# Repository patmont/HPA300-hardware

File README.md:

# HPA300 replacement controller hardware

An open-hardware, ESP32-S2 replacement control board for the Honeywell HPA300
air purifier. The board preserves the original front-panel layout while adding
USB-C, native USB programming, and a controller designed for the companion
[HPA300 firmware](https://github.com/patmont/HPA300-firmware).

> [!IMPORTANT]
> This is an independent community project. It is not affiliated with,
> authorized by, or endorsed by Honeywell International Inc. Build and install
> it at your own risk.

## Downloads

| I want to... | Get this |
| --- | --- |
| Read the circuit | [Schematic PDF](HPA300.pdf) |
| Order the parts | [DigiKey shared list](https://www.digikey.com/en/mylists/list/1ANK154NOU) or [versioned BOM](manufacturing/Assembly/HPA300-bom.csv) |
| Order a bare PCB | Download the `HPA300-<version>-gerbers.zip` asset from the [latest release](https://github.com/patmont/HPA300-hardware/releases/latest) |
| Modify the design | Open [HPA300.kicad_pro](HPA300.kicad_pro) in KiCad 9 |
| Build or flash firmware | Visit [HPA300-firmware](https://github.com/patmont/HPA300-firmware) |

Release assets are the recommended manufacturing handoff because they are tied
to a tagged revision and include SHA-256 checksums. The files under
`manufacturing/` are reviewable snapshots; do not mix them with source files
from a different commit.

## Hardware overview

- ESP32-S2-SOLO-2 controller with native USB-C
- Six capacitive-touch keys matching the original control panel
- Nine front-panel indicators with PWM brightness control
- 74HC238 fan-speed selection with a hardware-disabled default state
- Boot, reset, Tag-Connect programming, and power test access
- Two-layer, 1.6 mm PCB designed in KiCad 9
- Approximately 245 mm × 51 mm overall outline, including the shaped edges

The current checked-in design is revision A and corresponds to the as-built
board. Before ordering, inspect the schematic, board outline, connector
orientation, and your purifier revision. This project has not been evaluated or
certified by a safety agency.

## Manufacturing

For a bare PCB, upload only the release's Gerber archive to the fabricator. It
contains copper, solder mask, paste, silkscreen, edge cuts, plated drills, and
non-plated drills. The archive is generated from the tracked files in
[`manufacturing/Fabrication`](manufacturing/Fabrication/).

The [DigiKey list](https://www.digikey.com/en/mylists/list/1ANK154NOU) is the
most convenient shopping list. The repository BOM is version controlled so a
release remains reproducible even if the shared list later changes. Check stock,
manufacturer part numbers, substitutions, and do-not-populate items before
ordering.

The current repository does **not** claim to be a turnkey PCBA package. An
assembly house will also need a placement/centroid file, confirmed rotations,
assembly drawings, and instructions for the through-hole and mechanical parts.
See [manufacturing/README.md](manufacturing/README.md) for the artifact manifest
and release procedure.

To build the same release assets locally from PowerShell:

```powershell
./scripts/package-release.ps1 -Version v0.1.0
```

The packages are written to `dist/`, which is intentionally ignored by Git.
Pushing a `v*` tag runs the same packager in GitHub Actions and creates a GitHub
release with the Gerber ZIP, schematic PDF, BOM, license notice, and checksum
manifest.

## Repository layout

```text
HPA300.kicad_pro         KiCad project entry point
HPA300.kicad_pcb         Editable PCB source
HPA300.kicad_sch         Root schematic and hierarchical sheets
*.kicad_sch
lib/                     Project-specific symbols, footprints, and 3D models
graphics/                Board renders, logo, and open-hardware mark
manufacturing/
  Fabrication/           Gerber and drill snapshot
  Assembly/              Version-controlled BOM
scripts/                 Reproducible release packaging
.github/workflows/       CI and tagged-release automation
```

KiCad backups, local preferences, caches, downloaded datasheets, and generated
release archives are excluded from version control. Custom symbols, footprints,
and 3D models required to open the project are kept in `lib/`.

## Contributing

Open an issue before making a change that affects the board outline, original
appliance interface, fan safety behavior, or manufacturing stack-up. For a
design change, update the editable KiCad source first, run KiCad's electrical
and design-rule checks, then regenerate the PDF, BOM, Gerbers, and drill files
together. Include the KiCad version and rule-check results in the pull request.

## License and attribution

The hardware design and associated source are licensed under the
[CERN Open Hardware Licence Version 2 – Weakly Reciprocal](LICENSE). You may
study, modify, make, and sell products based on the design, but the license
requires preservation of notices and corresponding-source obligations. See
[NOTICE.md](NOTICE.md) for the copyright, source-location, attribution, and
trademark notices that travel with the design.

Commercial use cannot be prohibited while also calling the project open-source
hardware. The reciprocal license and source-location notice are intended to
ensure that commercial derivatives remain attributable and that their design
changes are available to recipients.

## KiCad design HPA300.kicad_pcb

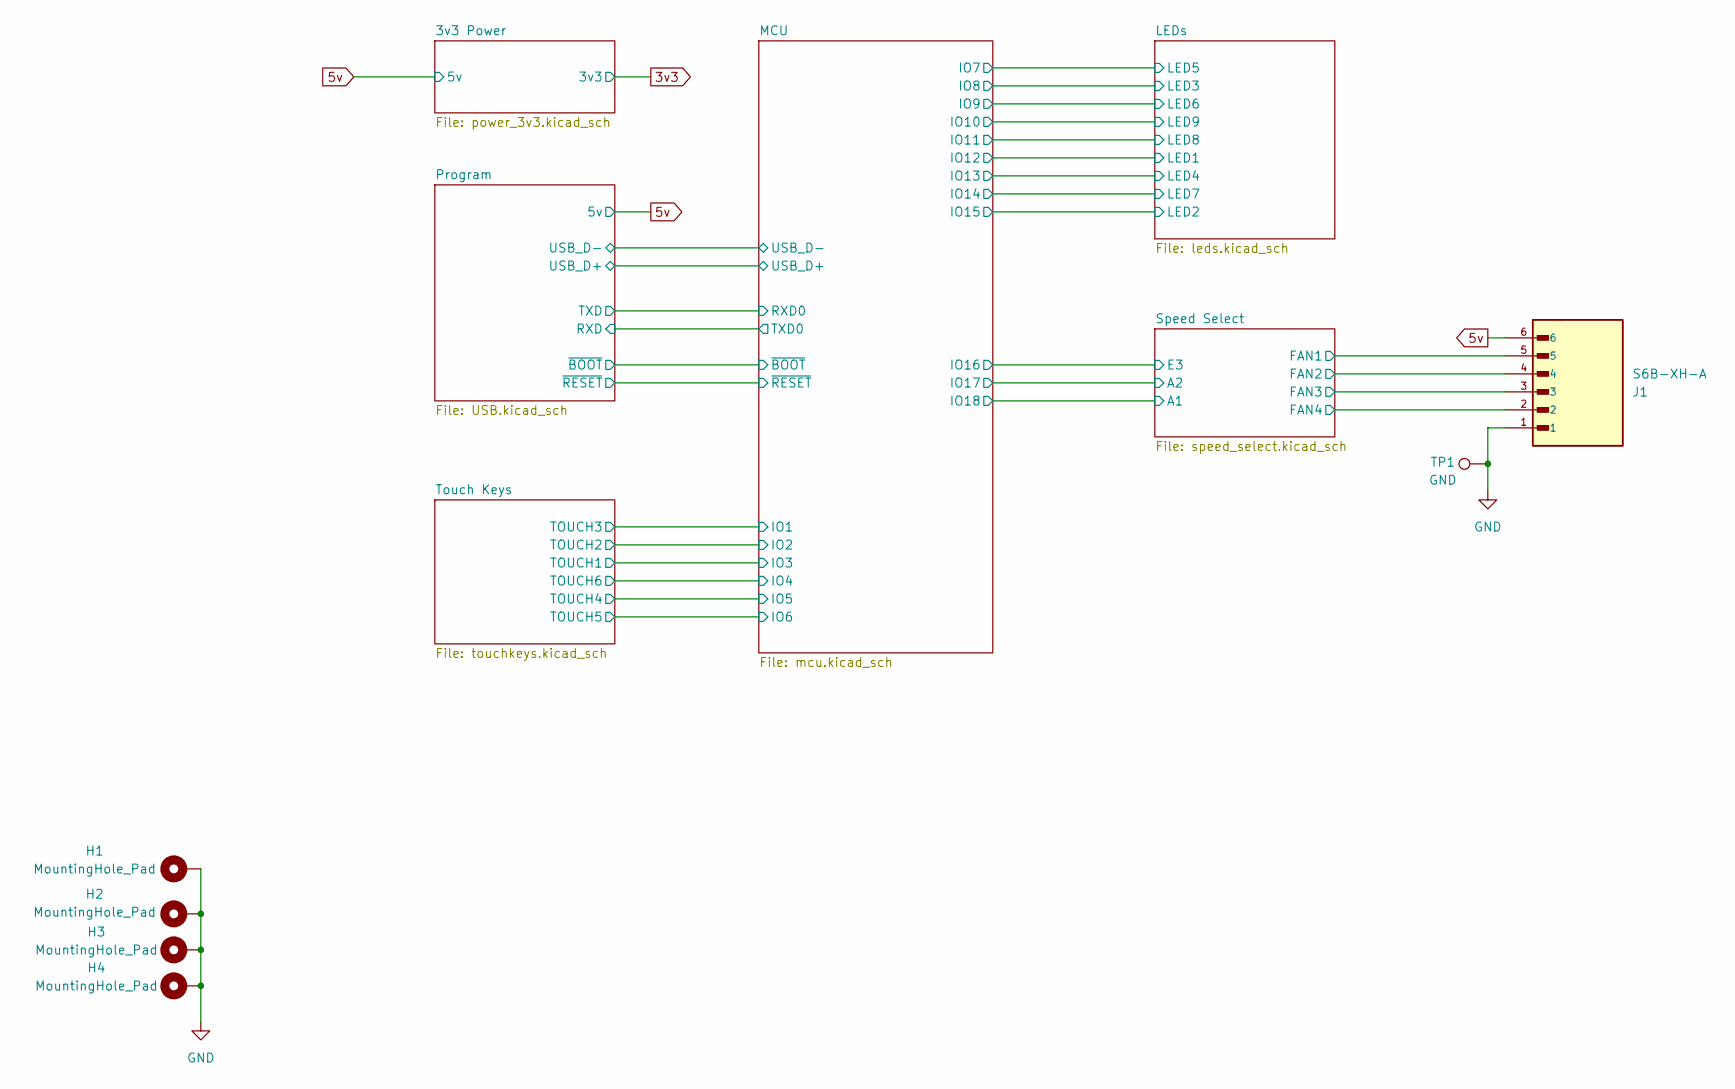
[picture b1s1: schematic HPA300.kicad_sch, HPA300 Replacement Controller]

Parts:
H1, H2, H3, H4: MountingHole_Pad; MountingHole_3.5mm_Pad_Via
J1: S6B-XH-A; JST_S6B-XH-A; Digikey S6B-XH-A
TP1: GND; TestPoint_Pad_D1.0mm

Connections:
5v: J1.6; also elsewhere on the board
/Speed Select/FAN1: J1.5; also elsewhere on the board
/Speed Select/FAN2: J1.4; also elsewhere on the board
/Speed Select/FAN3: J1.3; also elsewhere on the board
/Speed Select/FAN4: J1.2; also elsewhere on the board
GND: H1.1, H2.1, H3.1, H4.1, J1.1, TP1.1; also elsewhere on the board

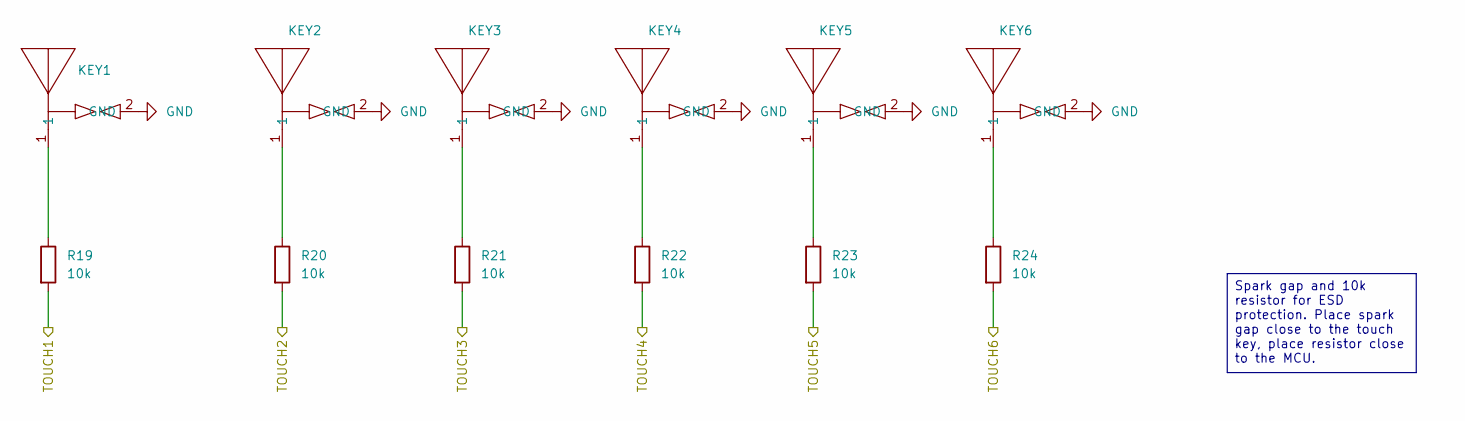
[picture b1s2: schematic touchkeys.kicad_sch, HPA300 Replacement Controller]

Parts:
KEY1, KEY2, KEY3, KEY4, KEY5, KEY6: HPA300 Key
R19, R20, R21, R22, R23, R24: 10k; R_0805_2012Metric; Digikey CRCW080510K0FKEA

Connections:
/MCU/IO1: R21.2; also elsewhere on the board
/MCU/IO2: R20.2; also elsewhere on the board
/MCU/IO3: R19.2; also elsewhere on the board
/MCU/IO4: R24.2; also elsewhere on the board
/MCU/IO5: R22.2; also elsewhere on the board
/MCU/IO6: R23.2; also elsewhere on the board
GND: KEY1.2 (GND), KEY2.2 (GND), KEY3.2 (GND), KEY4.2 (GND), KEY5.2 (GND), KEY6.2 (GND); also elsewhere on the board
unnamed: KEY1.1, R19.1
unnamed: KEY2.1, R20.1
unnamed: KEY3.1, R21.1
unnamed: KEY4.1, R22.1
unnamed: KEY5.1, R23.1
unnamed: KEY6.1, R24.1

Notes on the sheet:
Spark gap and 10k resistor for ESD protection. Place spark gap close to the touch key, place resistor close to the MCU.

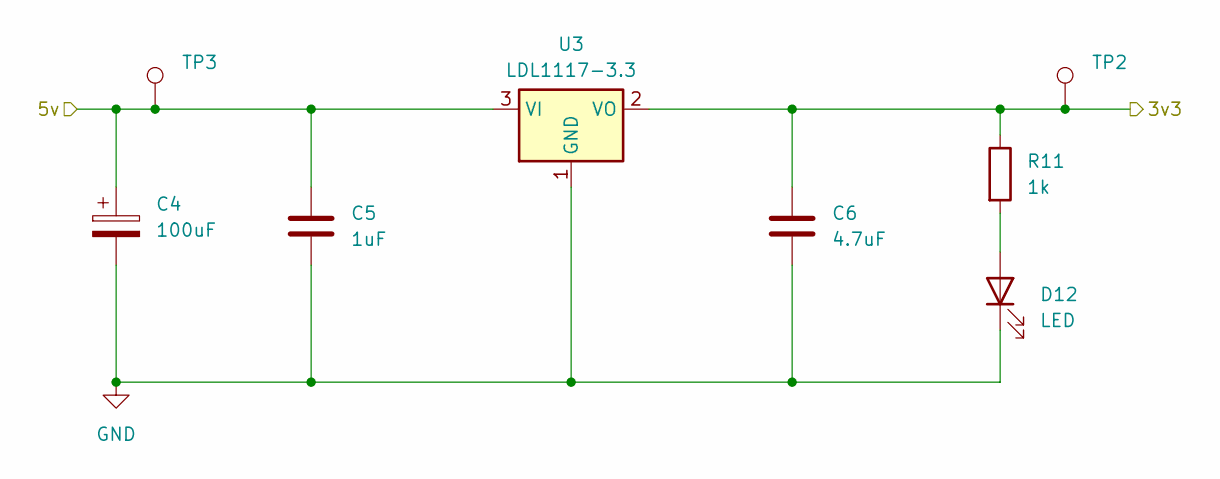
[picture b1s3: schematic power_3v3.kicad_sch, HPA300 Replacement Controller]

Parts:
C4: 100uF; CP_Elec_6.3x5.8; Digikey UUD1C101MCL1GS
C5: 1uF; C_0805_2012Metric; Digikey GRM21BR61C105MA01L
C6: 4.7uF; C_1206_3216Metric; Digikey GRM319R61H475KA12D
D12: LED; LED_0805_2012Metric; Digikey LTST-C170GKT
R11: 1k; R_0805_2012Metric; Digikey CRCW08051K00FKEA
TP2: 3.3V; TestPoint_Pad_D1.0mm
TP3: 5V; TestPoint_Pad_D1.0mm
U3: LDL1117-3.3; SOT-223-3_TabPin2; Digikey LDL1117S33R

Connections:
3v3: C6.1, R11.1, TP2.1, U3.2 (VO); also elsewhere on the board
5v: C4.1, C5.1, TP3.1, U3.3 (VI); also elsewhere on the board
GND: C4.2, C5.2, C6.2, D12.1 (K), U3.1 (GND); also elsewhere on the board
unnamed: D12.2 (A), R11.2

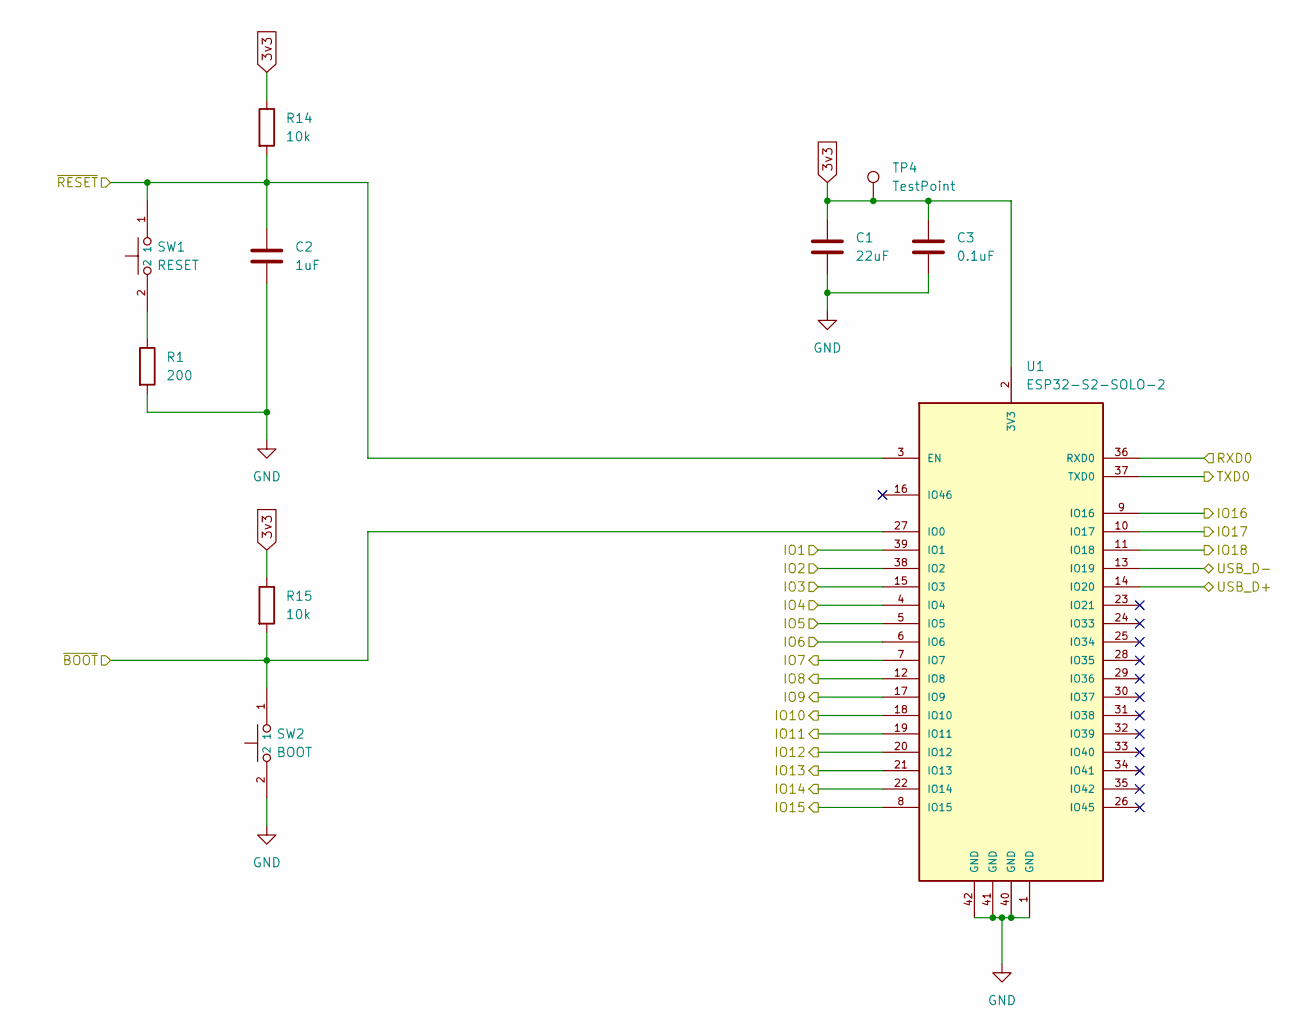
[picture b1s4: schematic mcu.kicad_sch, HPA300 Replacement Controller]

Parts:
C1: 22uF; C_1206_3216Metric; Digikey CL31A226KAHNNNE
C2: 1uF; C_0805_2012Metric; Digikey GRM21BR61C105MA01L
C3: 0.1uF; C_0805_2012Metric; Digikey KGM21KR51H104KU
R1: 200; R_0805_2012Metric; Digikey CRCW0805200RFKEAC
R14, R15: 10k; R_0805_2012Metric; Digikey CRCW080510K0FKEA
SW1: RESET; SW_B3U-1100P; Digikey B3U-1100P
SW2: BOOT; SW_B3U-1100P; Digikey B3U-1100P
TP4: TestPoint; TestPoint_Pad_D1.0mm
U1: ESP32-S2-SOLO-2; PARTREV 1.6; Digikey ESP32-S2-SOLO-2-N4

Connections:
3v3: C1.1, C3.1, R14.1, R15.1, TP4.1, U1.2 (3V3); also elsewhere on the board
/LEDs/LED1: U1.20 (IO12); also elsewhere on the board
/LEDs/LED2: U1.8 (IO15); also elsewhere on the board
/LEDs/LED3: U1.12 (IO8); also elsewhere on the board
/LEDs/LED4: U1.21 (IO13); also elsewhere on the board
/LEDs/LED5: U1.7 (IO7); also elsewhere on the board
/LEDs/LED6: U1.17 (IO9); also elsewhere on the board
/LEDs/LED7: U1.22 (IO14); also elsewhere on the board
/LEDs/LED8: U1.19 (IO11); also elsewhere on the board
/LEDs/LED9: U1.18 (IO10); also elsewhere on the board
/MCU/IO1: U1.39 (IO1); also elsewhere on the board
/MCU/IO2: U1.38 (IO2); also elsewhere on the board
/MCU/IO3: U1.15 (IO3); also elsewhere on the board
/MCU/IO4: U1.4 (IO4); also elsewhere on the board
/MCU/IO5: U1.5 (IO5); also elsewhere on the board
/MCU/IO6: U1.6 (IO6); also elsewhere on the board
/MCU/IO16: U1.9 (IO16); also elsewhere on the board
/MCU/IO17: U1.10 (IO17); also elsewhere on the board
/MCU/IO18: U1.11 (IO18); also elsewhere on the board
/MCU/RXD0: U1.36 (RXD0); also elsewhere on the board
/MCU/TXD0: U1.37 (TXD0); also elsewhere on the board
/MCU/USB_D+: U1.14 (IO20); also elsewhere on the board
/MCU/USB_D-: U1.13 (IO19); also elsewhere on the board
/MCU/~BOOT: R15.2, SW2.1, U1.27 (IO0); also elsewhere on the board
/MCU/~RESET: C2.1, R14.2, SW1.1, U1.3 (EN); also elsewhere on the board
GND: C1.2, C2.2, C3.2, R1.2, SW2.2, U1.1 (GND), U1.40 (GND), U1.41 (GND), U1.42 (GND); also elsewhere on the board
unnamed: R1.1, SW1.2

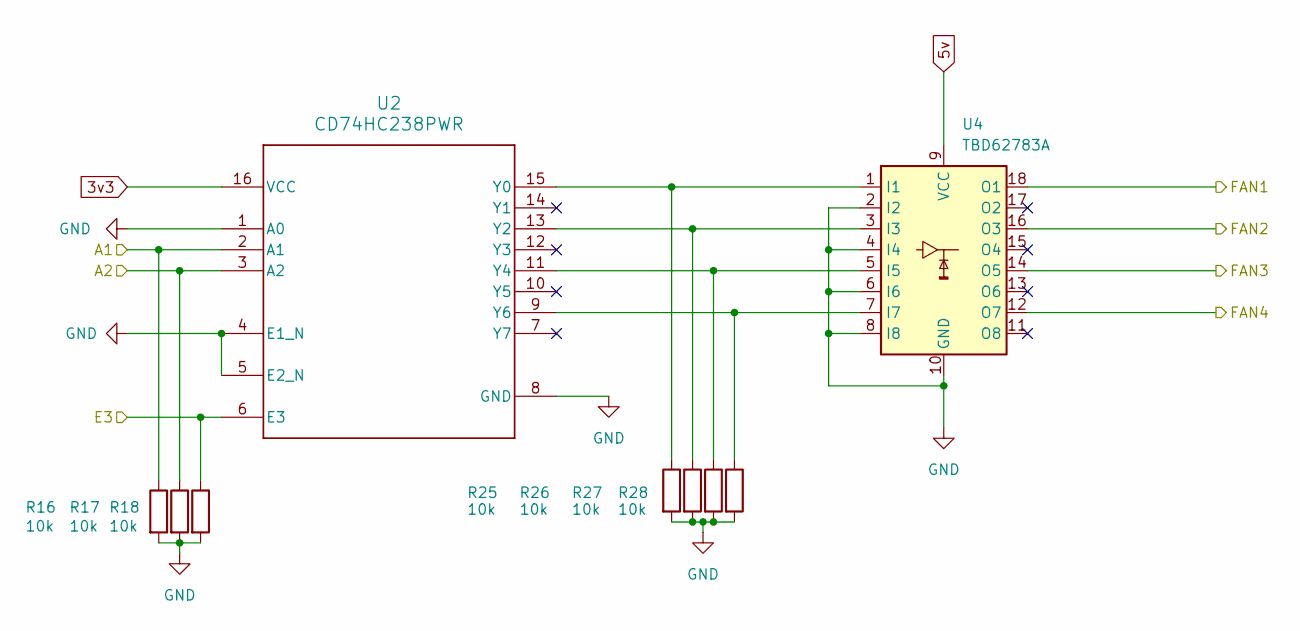
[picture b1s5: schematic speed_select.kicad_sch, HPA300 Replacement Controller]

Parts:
R16, R17, R18, R25, R26, R27, R28: 10k; R_0805_2012Metric; Digikey CRCW080510K0FKEA
U2: CD74HC238PWR; PW0016A_N; Digikey CD74HC238PWR
U4: TBD62783A; SSOP-18_4.4x6.5mm_P0.65mm; Digikey TBD62783AFNG,EL

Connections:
3v3: U2.16 (VCC); also elsewhere on the board
5v: U4.9 (VCC); also elsewhere on the board
/MCU/IO16: R18.1, U2.6 (E3); also elsewhere on the board
/MCU/IO17: R17.1, U2.3 (A2); also elsewhere on the board
/MCU/IO18: R16.1, U2.2 (A1); also elsewhere on the board
/Speed Select/FAN1: U4.18 (O1); also elsewhere on the board
/Speed Select/FAN2: U4.16 (O3); also elsewhere on the board
/Speed Select/FAN3: U4.14 (O5); also elsewhere on the board
/Speed Select/FAN4: U4.12 (O7); also elsewhere on the board
GND: R16.2, R17.2, R18.2, R25.2, R26.2, R27.2, R28.2, U2.1 (A0), U2.4 (E1_N), U2.5 (E2_N), U2.8 (GND), U4.2 (I2), U4.4 (I4), U4.6 (I6), U4.8 (I8), U4.10 (GND); also elsewhere on the board
unnamed: R25.1, U2.15 (Y0), U4.1 (I1)
unnamed: R26.1, U2.13 (Y2), U4.3 (I3)
unnamed: R27.1, U2.11 (Y4), U4.5 (I5)
unnamed: R28.1, U2.9 (Y6), U4.7 (I7)

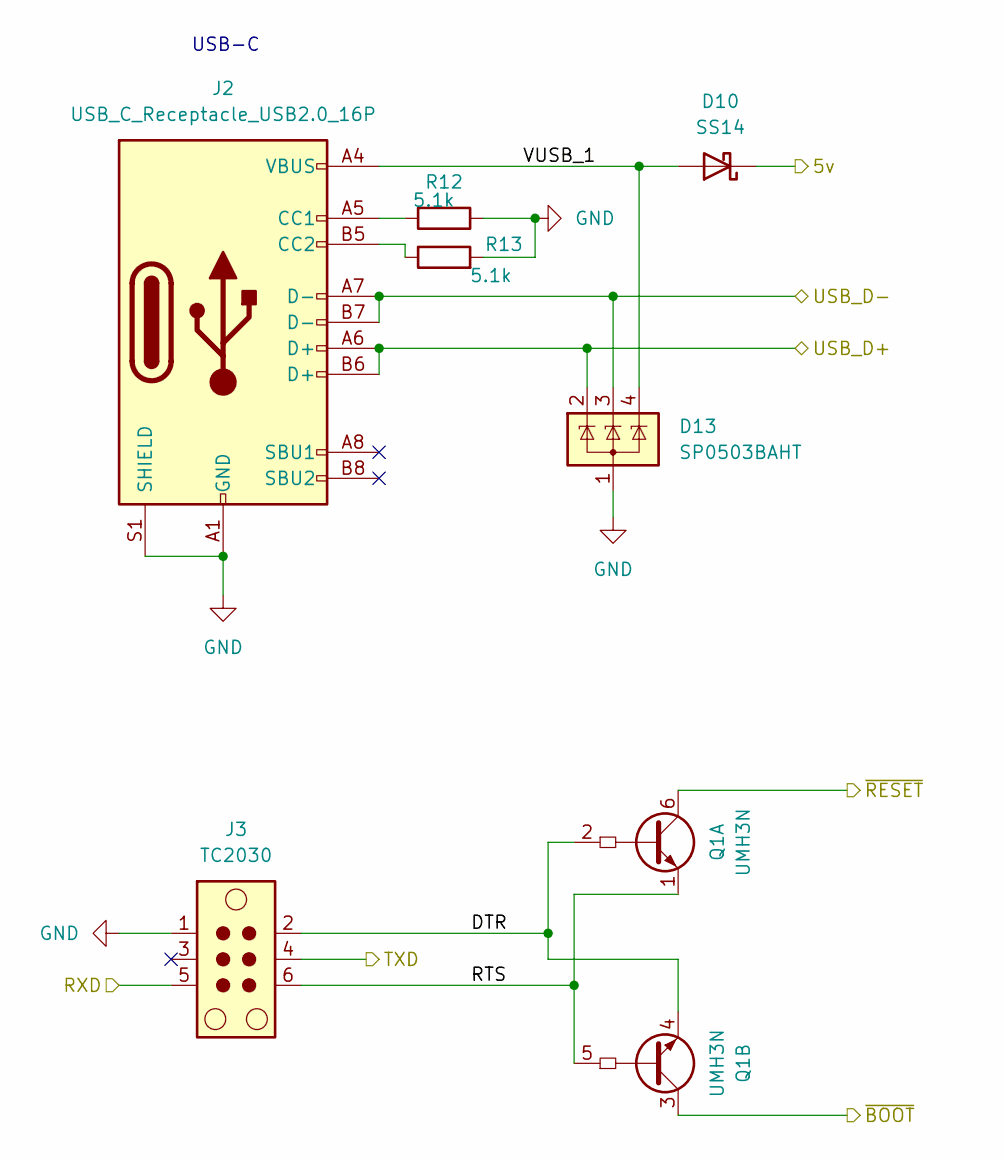
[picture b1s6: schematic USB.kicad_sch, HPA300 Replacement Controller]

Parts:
D10: SS14; D_SMA; Digikey B140Q-13-F
D13: SP0503BAHT; SOT-143; Digikey SP0503BAHTG
J2: USB_C_Receptacle_USB2.0_16P; USB_C_Receptacle_GCT_USB4110; Digikey USB4110-GF-A
J3: TC2030; Tag-Connect_TC2030-IDC-NL_2x03_P1.27mm_Vertical
Q1: UMH3N; SOT-363_SC-70-6; Digikey UMH3NFHATN
R12, R13: 5.1k; R_0805_2012Metric; Digikey CRCW08055K10FKEA

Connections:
5v: D10.1 (K); also elsewhere on the board
/MCU/RXD0: J3.4; also elsewhere on the board
/MCU/TXD0: J3.5; also elsewhere on the board
/MCU/USB_D+: D13.2 (K), J2.A6 (D+), J2.B6 (D+); also elsewhere on the board
/MCU/USB_D-: D13.3 (K), J2.A7 (D-), J2.B7 (D-); also elsewhere on the board
/MCU/~BOOT: Q1.3 (C2); also elsewhere on the board
/MCU/~RESET: Q1.6 (C1); also elsewhere on the board
/Program/DTR: J3.2, Q1.2 (B1), Q1.4 (E2)
/Program/RTS: J3.6, Q1.1 (E1), Q1.5 (B2)
/Program/VUSB_1: D10.2 (A), D13.4 (K), J2.A4 (VBUS), J2.A9 (VBUS), J2.B4 (VBUS), J2.B9 (VBUS)
GND: D13.1 (A), J2.A1 (GND), J2.A12 (GND), J2.B1 (GND), J2.B12 (GND), J2.S1 (SHIELD), J3.1, R12.1, R13.2; also elsewhere on the board
unnamed: J2.A5 (CC1), R12.2
unnamed: J2.B5 (CC2), R13.1

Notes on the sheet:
USB-C

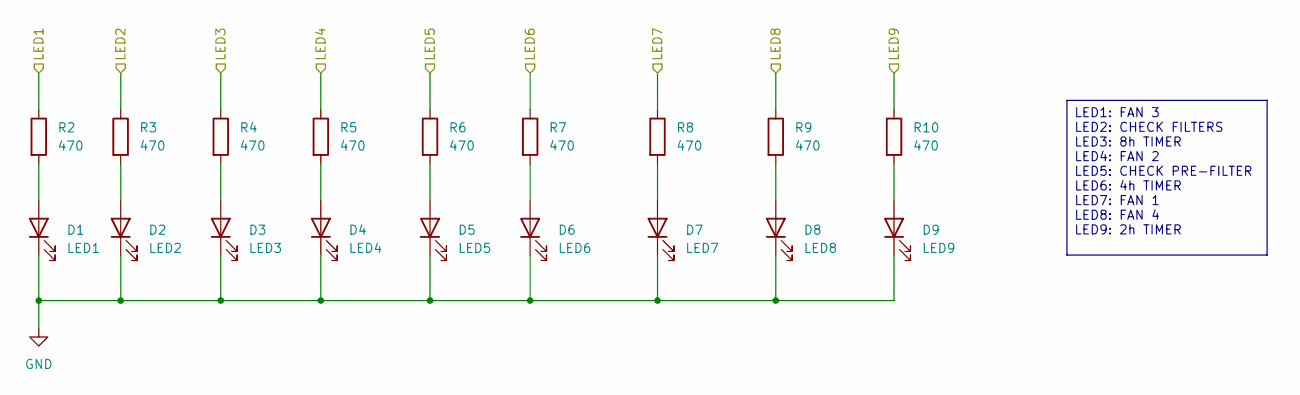
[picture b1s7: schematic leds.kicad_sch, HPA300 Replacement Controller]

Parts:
D1: LED1; LED_D3.0mm; Digikey 151031SS04000
D2: LED2; LED_D3.0mm; Digikey 151031SS04000
D3: LED3; LED_D3.0mm; Digikey 151031SS04000
D4: LED4; LED_D3.0mm; Digikey 151031SS04000
D5: LED5; LED_D3.0mm; Digikey 151031SS04000
D6: LED6; LED_D3.0mm; Digikey 151031SS04000
D7: LED7; LED_D3.0mm; Digikey 151031SS04000
D8: LED8; LED_D3.0mm; Digikey 151031SS04000
D9: LED9; LED_D3.0mm; Digikey 151031SS04000
R2, R3, R4, R5, R6, R7, R8, R9, R10: 470; R_0805_2012Metric; Digikey CRGCQ0805J470R

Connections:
/LEDs/LED1: R2.1; also elsewhere on the board
/LEDs/LED2: R3.1; also elsewhere on the board
/LEDs/LED3: R4.1; also elsewhere on the board
/LEDs/LED4: R5.1; also elsewhere on the board
/LEDs/LED5: R6.1; also elsewhere on the board
/LEDs/LED6: R7.1; also elsewhere on the board
/LEDs/LED7: R8.1; also elsewhere on the board
/LEDs/LED8: R9.1; also elsewhere on the board
/LEDs/LED9: R10.1; also elsewhere on the board
GND: D1.1 (K), D2.1 (K), D3.1 (K), D4.1 (K), D5.1 (K), D6.1 (K), D7.1 (K), D8.1 (K), D9.1 (K); also elsewhere on the board
unnamed: D1.2 (A), R2.2
unnamed: D2.2 (A), R3.2
unnamed: D3.2 (A), R4.2
unnamed: D4.2 (A), R5.2
unnamed: D5.2 (A), R6.2
unnamed: D6.2 (A), R7.2
unnamed: D7.2 (A), R8.2
unnamed: D8.2 (A), R9.2
unnamed: D9.2 (A), R10.2

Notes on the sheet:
LED1: FAN 3 LED2: CHECK FILTERS LED3: 8h TIMER LED4: FAN 2 LED5: CHECK PRE-FILTER LED6: 4h TIMER LED7: FAN 1 LED8: FAN 4 LED9: 2h TIMER

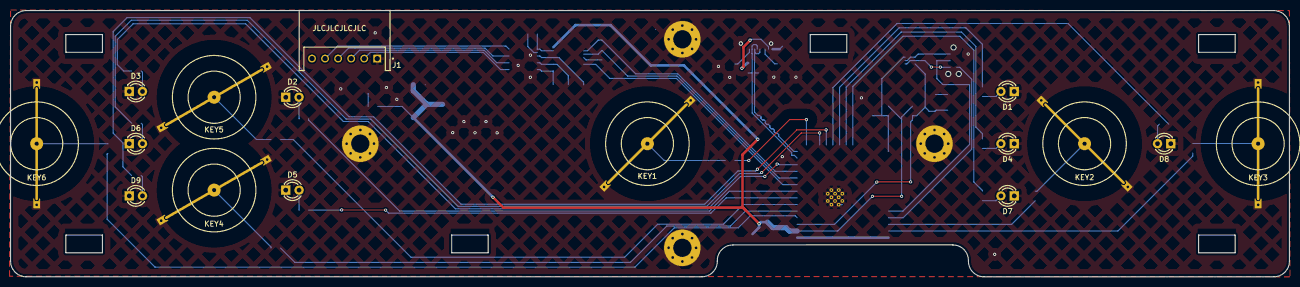
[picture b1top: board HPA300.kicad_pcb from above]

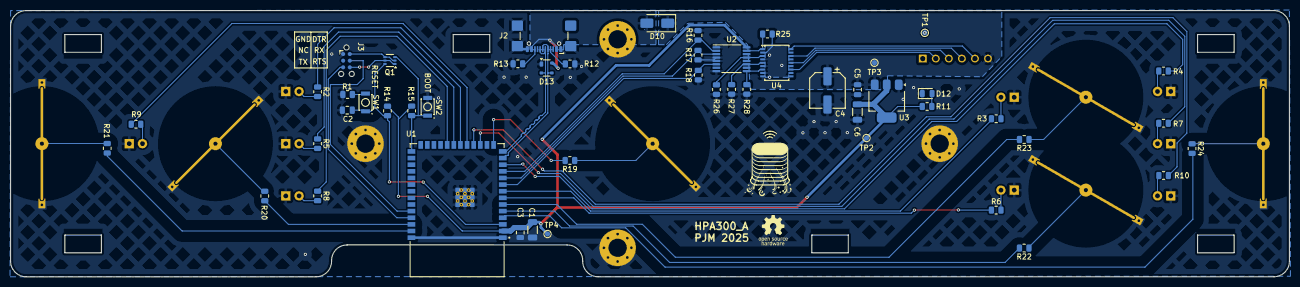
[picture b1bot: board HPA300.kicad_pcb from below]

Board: 2 copper layers, 245.0 x 51.0 mm, 70 parts (50 on the bottom side), 57 nets.

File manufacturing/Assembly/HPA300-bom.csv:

"Reference","Qty","Value","DNP","Exclude from BOM","Exclude from Board","Footprint","Datasheet","Digikey"
"C1","1","22uF","","","","Capacitor_SMD:C_1206_3216Metric","~","CL31A226KAHNNNE"
"C2,C5","2","1uF","","","","Capacitor_SMD:C_0805_2012Metric","~","GRM21BR61C105MA01L"
"C3","1","0.1uF","","","","Capacitor_SMD:C_0805_2012Metric","~","KGM21KR51H104KU"
"C4","1","100uF","","","","Capacitor_SMD:CP_Elec_6.3x5.8","https://www.nichicon.co.jp/english/series_items/catalog_pdf/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","UUD1C101MCL1GS"
"C6","1","4.7uF","","","","Capacitor_SMD:C_1206_3216Metric","~","GRM319R61H475KA12D"
"D1","1","LED1","","","","LED_THT:LED_D3.0mm","~","151031SS04000"
"D2","1","LED2","","","","LED_THT:LED_D3.0mm","~","151031SS04000"
"D3","1","LED3","","","","LED_THT:LED_D3.0mm","~","151031SS04000"
"D4","1","LED4","","","","LED_THT:LED_D3.0mm","~","151031SS04000"
"D5","1","LED5","","","","LED_THT:LED_D3.0mm","~","151031SS04000"
"D6","1","LED6","","","","LED_THT:LED_D3.0mm","~","151031SS04000"
"D7","1","LED7","","","","LED_THT:LED_D3.0mm","~","151031SS04000"
"D8","1","LED8","","","","LED_THT:LED_D3.0mm","~","151031SS04000"
"D9","1","LED9","","","","LED_THT:LED_D3.0mm","~","151031SS04000"
"D10","1","SS14","","","","Diode_SMD:D_SMA","https://www.vishay.com/docs/88746/ss12.pdf","B140Q-13-F"
"D12","1","LED","","","","LED_SMD:LED_0805_2012Metric","~","LTST-C170GKT"
"D13","1","SP0503BAHT","","","","Package_TO_SOT_SMD:SOT-143","http://www.littelfuse.com/~/media/files/littelfuse/technical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"," SP0503BAHTG"
"H1,H2,H3,H4","4","MountingHole_Pad","","Excluded from BOM","","MountingHole:MountingHole_3.5mm_Pad_Via","~",""
"J1","1","S6B-XH-A","","","","0_connector:JST_S6B-XH-A","","S6B-XH-A"
"J2","1","USB_C_Receptacle_USB2.0_16P","","","","Connector_USB:USB_C_Receptacle_GCT_USB4110","https://www.usb.org/sites/default/files/documents/usb_type-c.zip"," USB4110-GF-A"
"J3","1","TC2030","","Excluded from BOM","","Connector:Tag-Connect_TC2030-IDC-NL_2x03_P1.27mm_Vertical","https://www.tag-connect.com/wp-content/uploads/bsk-pdf-manag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",""
"KEY1,KEY2,KEY3,KEY4,KEY5,KEY6","6","~","","","","0_switch:HPA300 Key","",""
"Q1","1","UMH3N","","","","Package_TO_SOT_SMD:SOT-363_SC-70-6","http://rohmfs.rohm.com/en/products/databook/datasheet/discre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","UMH3NFHATN"
"R1","1","200","","","","Resistor_SMD:R_0805_2012Metric","~","CRCW0805200RFKEAC"
"R2,R3,R4,R5,R6,R7,R8,R9,R10","9","470","","","","Resistor_SMD:R_0805_2012Metric","~","CRGCQ0805J470R"
"R11","1","1k","","","","Resistor_SMD:R_0805_2012Metric","~","CRCW08051K00FKEA"
"R12,R13","2","5.1k","","","","Resistor_SMD:R_0805_2012Metric","~","CRCW08055K10FKEA"
"R14,R15,R16,R17,R18,R19,R20,R21,R22,R23,R24,R25,R26,R27,R28","15","10k","","","","Resistor_SMD:R_0805_2012Metric","~","CRCW080510K0FKEA"
"SW1","1","RESET","","","","0_switch:SW_B3U-1100P","","B3U-1100P"
"SW2","1","BOOT","","","","0_switch:SW_B3U-1100P","","B3U-1100P"
"TP1","1","GND","","","","TestPoint:TestPoint_Pad_D1.0mm","~",""
"TP2","1","3.3V","","","","TestPoint:TestPoint_Pad_D1.0mm","~",""
"TP3","1","5V","","","","TestPoint:TestPoint_Pad_D1.0mm","~",""
"TP4","1","TestPoint","","","","TestPoint:TestPoint_Pad_D1.0mm","~",""
"U1","1","ESP32-S2-SOLO-2","","","","0_mcu:ESP32-S2-SOLO-2","","ESP32-S2-SOLO-2-N4"
"U2","1","CD74HC238PWR","","","","0_74xx:PW0016A_N","https://www.ti.com/lit/gpn/cd74hc238","CD74HC238PWR"
"U3","1","LDL1117-3.3","","","","Package_TO_SOT_SMD:SOT-223-3_TabPin2","https://www.st.com/content/ccc/resource/technical/document/d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","LDL1117S33R"
"U4","1","TBD62783A","","","","Package_SO:SSOP-18_4.4x6.5mm_P0.65mm","http://toshiba.semicon-storage.com/info/docget.jsp?did=30523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","TBD62783AFNG,EL"

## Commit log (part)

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2025-11-24 Rev A as-built
    Release of the Rev A as-built board files

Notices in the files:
HPA300.kicad_pcb:
Open hardware — CERN-OHL-W-2.0
